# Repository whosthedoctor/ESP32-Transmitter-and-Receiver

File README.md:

# ESP32-Transmitter-and-Receiver

This is designed as a custom ESP32 transmitter and receiver that can use LoRA (2.4 GHz), FLRC, and GFSK protocols. 

My initial goal for this project was to simply make a custom transmitter and receiver for my custom FPV drone, as it was originally using the PCB radio on an ESP-32, but soon grew into a very complex PCB routing and schematic design project. 

I learned lots of useful techniques in KiCAD and JLCPCB and part selection, such as routing, layering, vias, copper pours, and constraints with RF signal routing, which I will use in my future to make even more complex PCBs!

The radio amplifier and transceiver module is based on the SX1280IMLTRT transceiver IC and an RFX2401C RF front-end.

In order to fit the requirements on my drone, instead of putting bulky screw holes, my goal for the entire board was to make it as small and efficient as possible.

# PCB + Wiring Diagram

I used KiCAD, as it is free, unlike something like Altium Designer, to design the PCB, find parts, and make schematics.

## Schematic

Full schematic PDF: [Schematic Files/ESPNOW_Reciever_and_Transmitter.pdf](Schematic%20Files/ESPNOW_Reciever_and_Transmitter.pdf)

## PCB
Gerbers and drill files are in `PCB Gerbers/`.

### Backside

### Frontside

### Topside

### Bottom

### JLCPCB Assembly Preview

## Wiring with Pins to ESP32 DevKit-C CP2012
| J1 Pin | Signal   | ESP32 GPIO | Notes                                        |
|:------:|----------|:----------:|----------------------------------------------|
| 1      | 5V       | 5V         | Power           |
| 2      | GND      | GND        |                                              |
| 3      | SCK      | GPIO18     | SPI clock (VSPI)                             |
| 4      | MISO     | GPIO19     | Output from SX1280                           |
| 5      | MOSI     | GPIO23     |                                              |
| 6      | NSS (CS) | GPIO5      |                                              |
| 7      | BUSY     | GPIO4      | Input to ESP32                               |
| 8      | DIO1     | GPIO27     | Interrupt input                              |
| 9      | RST      | GPIO13     |                                              |
| 10     | TXEN     | GPIO25     | To RFX2401C through R2                       |
| 11     | RXEN     | GPIO26     | To RFX2401C through R3                       |
| 12     | GND      | GND        | Connect both ground pins                     |

## BOM
[BOM.csv](https://github.com/user-attachments/files/35434525/BOM.csv)

## Additional Notes
Although this is a kind of uneventful and not world-changing project like some of the other ones, it was quite fun. A lot of my projects got rejected already :'(

The reason I will be using JLCPCB over PCBWay is due to the marketing and reputation of JLCPCB, and I can't manufacture the PCBs in-house as I don't have any experience with it or have the materials with assembly.

Also if there are files called ESP-NOW..., the project was unable to be renamed in KiCAD and I originally wanted it to use ESP-NOW, but that is a WiFi protocol and not LR enough.

I played Factorio a couple years back, beat it, played Krastorio and SE, and it was more similar than not to trace routing. Very fun to do, actually!

Antennas (Amazon): the receiver/drone antenna is the BOOBRIE 2.4GHz SMA male (B0991PKTDL), a 2-antenna pack, $6.68/pack ($3.34 each, better per-antenna rate than singles). One antenna per board, so 3 packs for 5 boards (1 spare). The transmitter/controller antenna is the HeelAooRC 2.4GHz ExpressLRS ES24TX Moxon (SMA plug, for the Micro TX module), also a 2-antenna pack, $14.99/pack, 1 pack for the controller (1 used, 1 spare).

I couldn't match the lapse times, as I work sporadically (work for 5 minutes, then play cs, then repeat), so a lot of the lapses don't represent all the work I did.

Really expensive because JLCPCB can't do any less than a 5 pack of boards.

## No Fixes Needed Notes
U3 Schematic symbol is LT1761-1.2 but AP2112K-3.3 is placed
 - The PCB is fine, just the Schematic DRC has an error
C18/C19 wire is missing in schematic, connected at node and error in DRC, prod is fine.
U2 RFX2401C has no 3D model in the STEP, but just check the one in KiCAD
 - 3D model only affects the render and STEP export

## Test Code

**UNTESTED**

No Hackatime, as it's a pretty short and basic script.

Both use [RadioLib](https://github.com/jgromes/RadioLib) and the J1 pins above. Radio settings (2400 MHz, 812.5 kHz BW, SF9, CR 4/7) must match on both boards.

### Transmitter

```cpp
#include <RadioLib.h>

#define PIN_SCK   18
#define PIN_MISO  19
#define PIN_MOSI  23
#define PIN_NSS    5
#define PIN_DIO1  27
#define PIN_RST   13
#define PIN_BUSY   4
#define PIN_TXEN  25
#define PIN_RXEN  26

SX1280 radio = new Module(PIN_NSS, PIN_DIO1, PIN_RST, PIN_BUSY);

const int8_t TX_POWER_DBM = 0;

uint32_t counter = 0;

void setup() {
  Serial.begin(115200);
  SPI.begin(PIN_SCK, PIN_MISO, PIN_MOSI, PIN_NSS);

  radio.setRfSwitchPins(PIN_RXEN, PIN_TXEN);

  // 2400 MHz, 812.5 kHz BW, SF9, CR 4/7, private sync word
  int state = radio.begin(2400.0, 812.5, 9, 7, RADIOLIB_SX128X_SYNC_WORD_PRIVATE, TX_POWER_DBM);
  if (state != RADIOLIB_ERR_NONE) {
    Serial.print("SX1280 init failed, code ");
    Serial.println(state);
    while (true) delay(1000);
  }
  Serial.println("Transmitter ready");
}

void loop() {
  String msg = "Hello #" + String(counter++);
  int state = radio.transmit(msg);
  if (state == RADIOLIB_ERR_NONE) {
    Serial.print("Sent: ");
    Serial.println(msg);
  } else {
    Serial.print("Send failed, code ");
    Serial.println(state);
  }
  delay(1000);
}
```

### Receiver

```cpp
#include <RadioLib.h>

#define PIN_SCK   18
#define PIN_MISO  19
#define PIN_MOSI  23
#define PIN_NSS    5
#define PIN_DIO1  27
#define PIN_RST   13
#define PIN_BUSY   4
#define PIN_TXEN  25
#define PIN_RXEN  26

SX1280 radio = new Module(PIN_NSS, PIN_DIO1, PIN_RST, PIN_BUSY);

volatile bool packetReady = false;

void IRAM_ATTR onPacket() {
  packetReady = true;
}

void setup() {
  Serial.begin(115200);
  SPI.begin(PIN_SCK, PIN_MISO, PIN_MOSI, PIN_NSS);
  radio.setRfSwitchPins(PIN_RXEN, PIN_TXEN);

  int state = radio.begin(2400.0, 812.5, 9, 7, RADIOLIB_SX128X_SYNC_WORD_PRIVATE, 0);
  if (state != RADIOLIB_ERR_NONE) {
    Serial.print("SX1280 init failed, code ");
    Serial.println(state);
    while (true) delay(1000);
  }

  radio.setPacketReceivedAction(onPacket);
  radio.startReceive();
  Serial.println("Receiver listening");
}

void loop() {
  if (!packetReady) return;
  packetReady = false;

  String msg;
  int state = radio.readData(msg);
  if (state == RADIOLIB_ERR_NONE) {
    Serial.print("Got: ");
    Serial.print(msg);
    Serial.print("  RSSI ");
    Serial.print(radio.getRSSI());
    Serial.print(" dBm  SNR ");
    Serial.print(radio.getSNR());
    Serial.println(" dB");
  } else if (state == RADIOLIB_ERR_CRC_MISMATCH) {
    Serial.println("Packet with bad CRC");
  } else {
    Serial.print("Receive failed, code ");
    Serial.println(state);
  }
  radio.startReceive();
}
```

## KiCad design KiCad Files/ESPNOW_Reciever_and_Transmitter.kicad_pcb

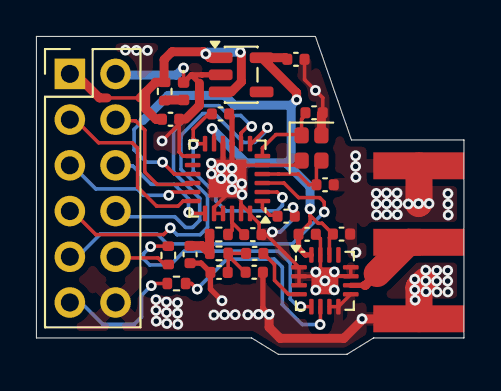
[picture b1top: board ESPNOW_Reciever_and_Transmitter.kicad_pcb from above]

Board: 2 copper layers, 23.8 x 17.7 mm, 25 parts (0 on the bottom side), 16 nets.

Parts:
C1: 10µF; C_0402_1005Metric
C2, C9, C10, C11: 0.1µF; C_0402_1005Metric
C3, C4: DNP; C_0402_1005Metric
C5: 1.2; C_0402_1005Metric
C6: 0.8pF; C_0402_1005Metric
C12: 1.2pF; C_0402_1005Metric
C13: 470nF; C_0402_1005Metric
C18: 100pF; C_0402_1005Metric
C19: 0.5pF; C_0402_1005Metric
D1: Red; LED_0402_1005Metric
J1: 2x6 female socket; PinHeader_2x06_P2.54mm_Vertical
J2: Amphenol 132289; SMA_Amphenol_132289_EdgeMount
L1: 3.0nH; R_0402_1005Metric
L2: 2.5nH; R_0402_1005Metric
R1, R2, R3: 1kΩ; R_0402_1005Metric
U1: SX1280IMLTRT; HVQFN-24-1EP_4x4mm_P0.5mm_EP2.1x2.1mm
U2: RFX2401C; HVQFN-16-1EP_3x3mm_P0.5mm_EP1.5x1.5mm
U3: AP2112K-3.3TRG1; TSOT-23-5
Y2: 52MHz; Crystal_SMD_2016-4Pin_2.0x1.6mm

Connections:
+3V3: C1.2, C9.1, C10.1, U1.11 (VBAT_IO), U1.15 (VBAT), U2.14 (VDD), U2.16 (VDD), U3.5 (VOUT)
GND: C1.1, C2.1, C3.1, C4.1, C5.1, C6.1, C9.2, C10.2, C11.1, C13.1, C18.1, C19.1, D1.1 (K), J1.12, J2.2 (Ext), U1.5 (GND), U1.9 (DIO2), U1.10 (DIO3), U1.13 (GND), U1.20 (GND), U1.21 (GND), U1.23 (GND), U1.24 (GND), U1.25 (GND), U2.1 (GND), U2.2 (GND), U2.3 (GND), U2.7 (GND), U2.8 (GND), U2.9 (GND), U2.11 (GND), U2.12 (GND), U2.15 (GND), U2.17 (EP), U3.2 (GND), Y2.2 (G), Y2.4 (G)
unnamed: C6.2, L1.2, L2.2
unnamed: C12.2, L2.1
unnamed: C18.2, C19.2
unnamed: D1.2 (A), R1.2
unnamed: C11.2, R1.1, U3.1 (VIN), U3.3 (~SHDN)
unnamed: J2.1 (In), U2.10 (ANT)
unnamed: C13.2, U1.2 (VDD_IN), U1.12 (DCC_FB)
unnamed: C5.2, L1.1, U1.22 (RFIO)
unnamed: C2.2, U1.1 (VR_PA)
unnamed: C4.2, U1.4 (XTA), Y2.3
unnamed: C3.2, U1.6 (XTB), Y2.1
unnamed: R3.2, U2.6 (RXEN)
unnamed: R2.2, U2.5 (TXEN)
unnamed: C12.1, U2.4 (TXRX)
